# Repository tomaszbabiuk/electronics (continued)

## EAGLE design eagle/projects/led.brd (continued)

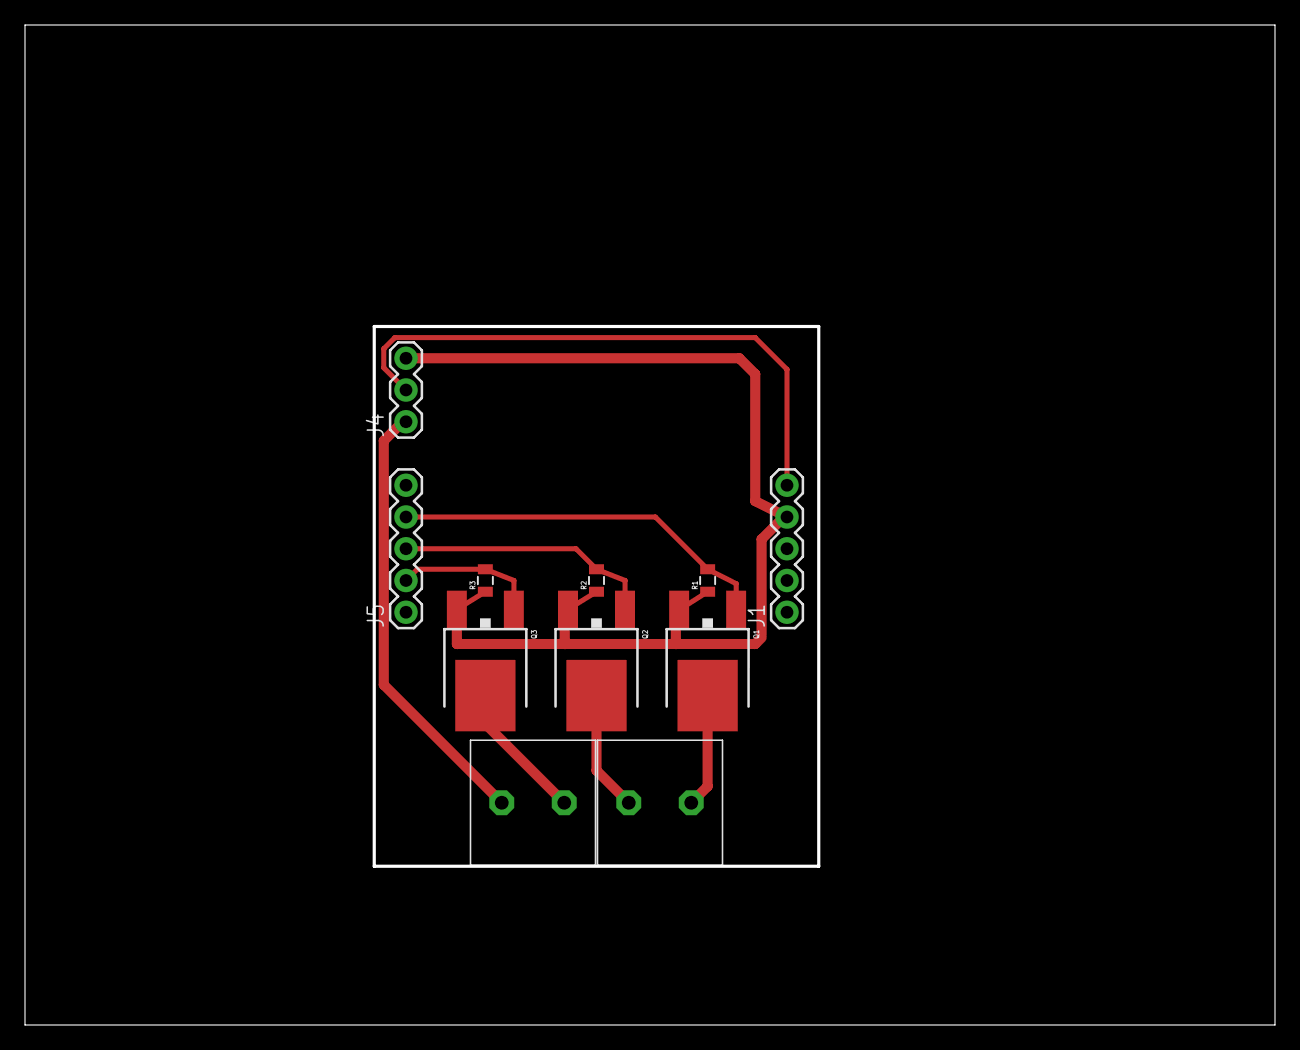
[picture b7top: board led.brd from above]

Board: 2 copper layers, 100.0 x 80.0 mm, 11 parts (0 on the bottom side), 9 nets.

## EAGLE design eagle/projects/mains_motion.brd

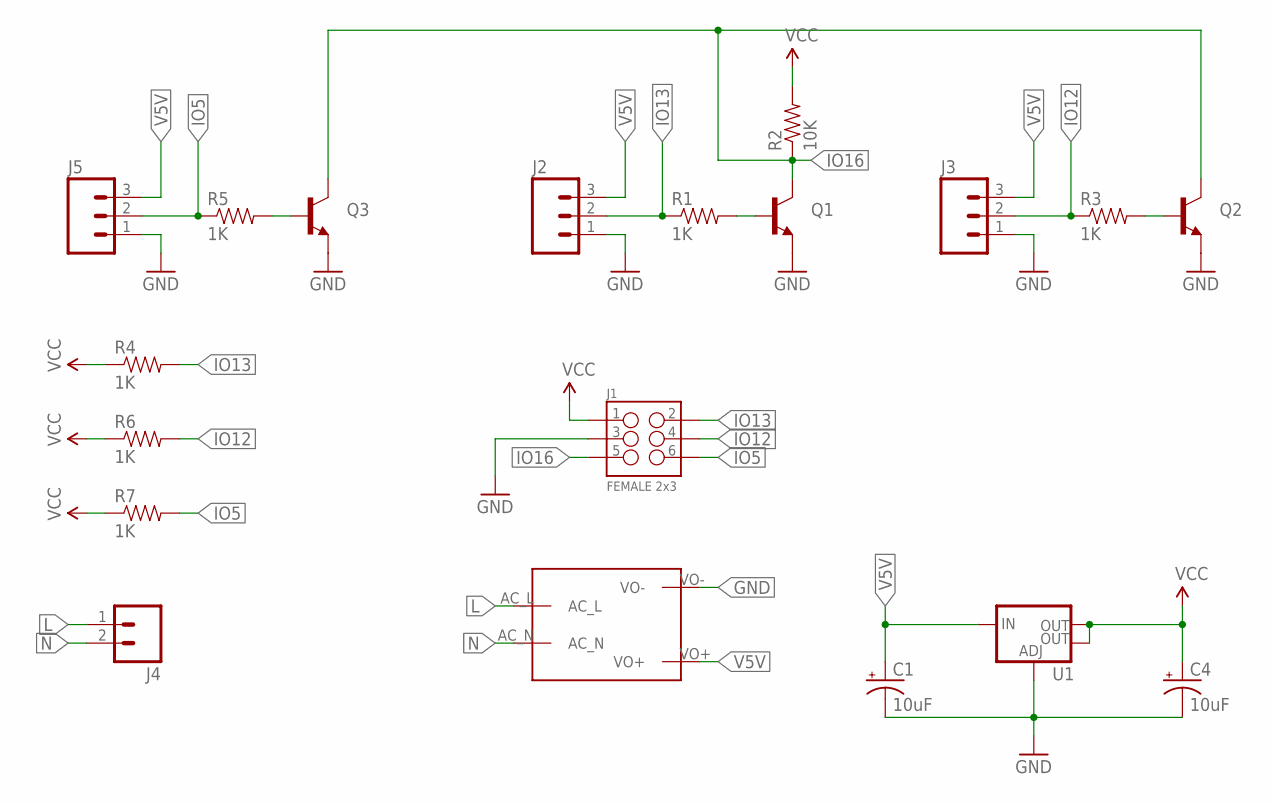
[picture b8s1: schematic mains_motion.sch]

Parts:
C1, C4: 10uF; EIA3216-KIT
J1: FEMALE 2x3; 2X3-SHROUDED
J2, J3, J5: M03PTH; 1X03
J4: M023.5MM; SCREWTERMINAL-3.5MM-2
Q1, Q2, Q3: TRANSISTOR_NPNSOT23-3; SOT23-3
R1, R3, R4, R5, R6, R7: 1K; 0805
R2: 10K; 0805
U1: V_REG_LM1117SOT223; SOT223
U$1: MAINS_CONVERTERS; HLK-PM01

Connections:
GND: C1.C (-), C4.C (-), J1.3, J2.1, J3.1, J5.1, Q1.2 (E), Q2.2 (E), Q3.2 (E), U1.1 (ADJ), U$1.VO-
IO5: J1.6, J5.2, R5.1, R7.2
IO12: J1.4, J3.2, R3.1, R6.2
IO13: J1.2, J2.2, R1.1, R4.2
IO16: J1.5, Q1.3 (C), Q2.3 (C), Q3.3 (C), R2.1
L: J4.1, U$1.AC_L
N: J4.2, U$1.AC_N
unnamed: Q2.1 (B), R3.2
unnamed: Q3.1 (B), R5.2
unnamed: Q1.1 (B), R1.2
V5V: C1.A (+), J2.3, J3.3, J5.3, U1.3 (IN), U$1.VO+
VCC: C4.A (+), J1.1, R2.2, R4.1, R6.1, R7.1, U1.2 (OUT), U1.4 (OUT)

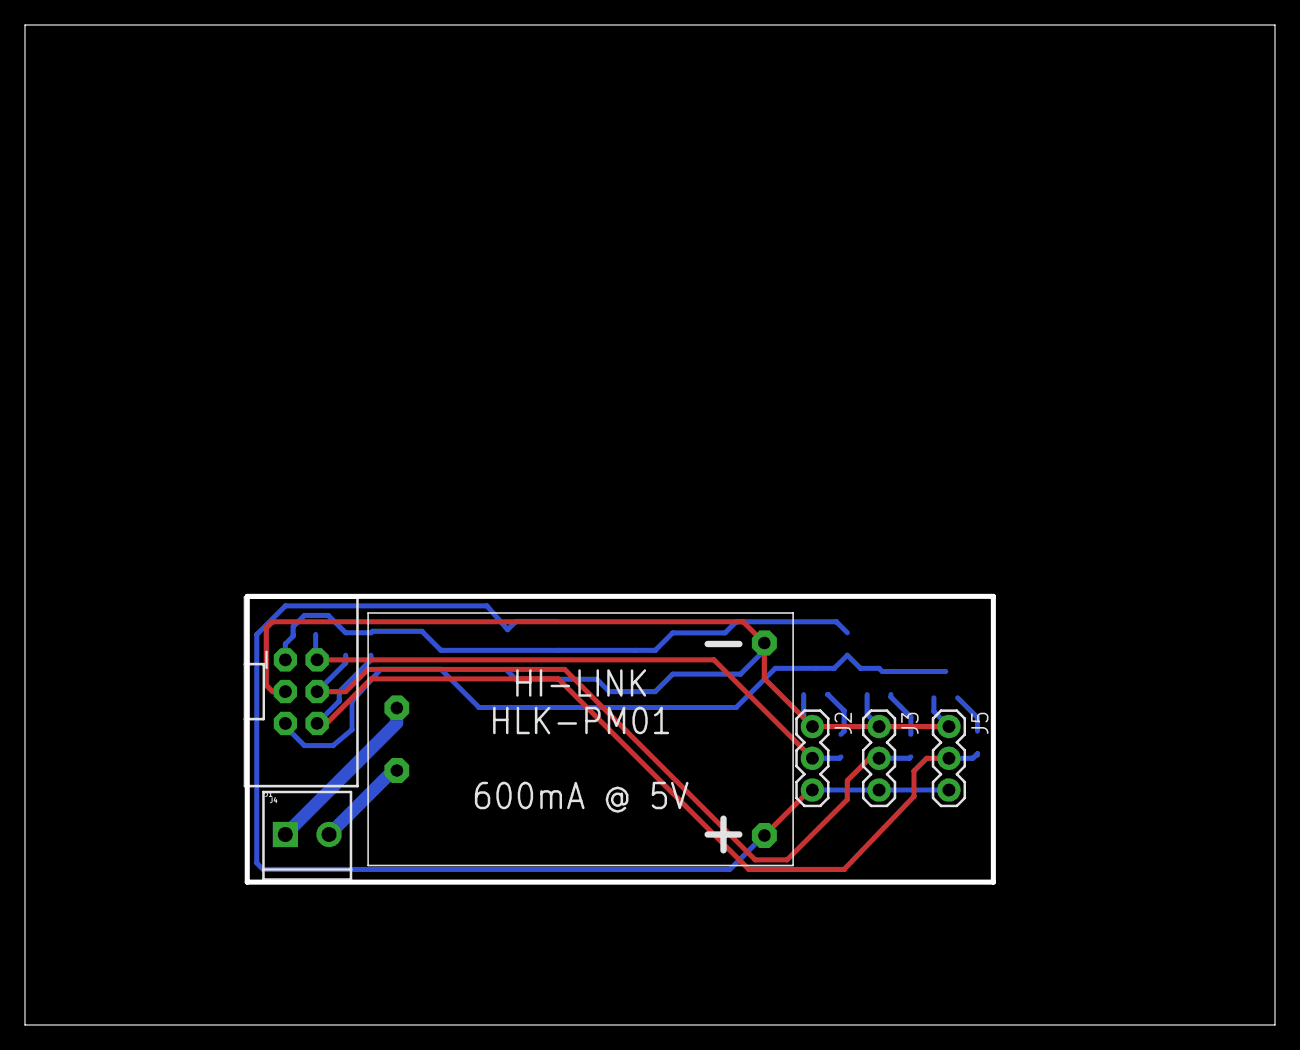
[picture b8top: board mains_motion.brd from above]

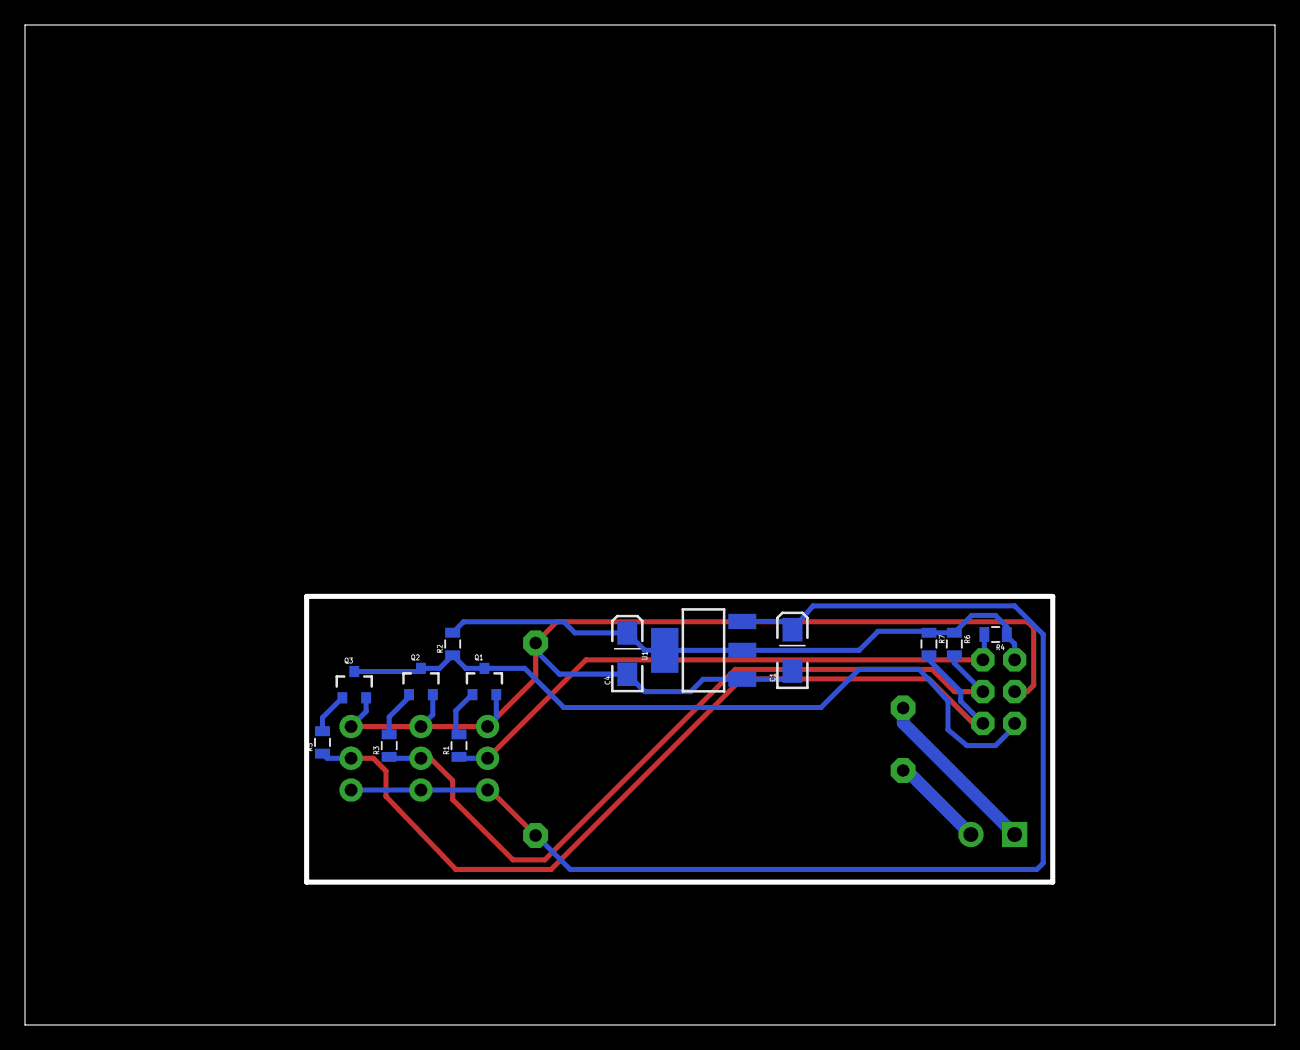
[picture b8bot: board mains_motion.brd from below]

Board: 2 copper layers, 100.0 x 80.0 mm, 19 parts (13 on the bottom side), 12 nets.

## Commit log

2019-09-19 Create LICENSE
2019-09-19 importing old eagle projects from unfuddle
